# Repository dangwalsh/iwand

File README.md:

# iWand

iWand is a hand-held device that identifies the color of an object it's pointed at. Point it at something, press the button, and it announces the color out loud.

## Repo layout

- [`firmware/`](firmware/README.md) — embedded code for the Seeed XIAO ESP32S3, using a GY-33 color sensor and a DFPlayer Mini + speaker for audio announcement
- [`electrical/`](electrical/README.md) — KiCad project: schematic, routed 75.9 × 22 mm two-layer PCB, project footprint library (`iwand.pretty`), 3D models, and ready-to-order Gerbers (`fab/iwand-gerbers.zip`)
- [`mechanical/`](mechanical/README.md) — enclosure design in Onshape, with a STEP model of the populated PCB (`iwand-pcb.step`) exported from KiCad

Each directory's README has setup/dependency details specific to that part of the project; [`CLAUDE.md`](CLAUDE.md) has the full architecture writeup (wake/sleep flow, pin assignments, library APIs).

## Status

- **Firmware:** a single-file sketch. It runs on hardware with calibration and spoken prompts. The battery-voltage monitor (D10) isn't read yet.
- **Electrical:** the PCB is routed and passes KiCad's design rules and schematic parity checks, with Gerbers ready to order. It hasn't been built or tested yet.
- **Mechanical:** enclosure design in Onshape has just started, from the exported PCB model. The layout along the wand, the component sizes and the required openings are in `mechanical/README.md`.

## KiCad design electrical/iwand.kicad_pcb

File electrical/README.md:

# iWand Electrical

KiCad schematic for the iWand color-identifying wand (Seeed XIAO ESP32S3 + GY-33 color sensor + DFPlayer Mini + AO3400 power gating). See `firmware/CLAUDE.md` for how the pin assignments here map to the firmware.

## Dependencies

- **KiCad 7.0 or newer** (developed with KiCad 10). The schematic (`iwand.kicad_sch`) is in the KiCad 7 s-expression format (`version 20230121`). Older KiCad versions won't open it.

The module symbols (`wand_parts:XIAO_ESP32S3`, `wand_parts:DFPlayer_Mini`) are embedded directly in `iwand.kicad_sch`, so there's no external symbol library to install. ERC warns that the `wand_parts` library isn't configured and that `Device:Q_NMOS_GDS` is missing from KiCad's current `Device` library. Both warnings are harmless, because the embedded copies are used.

## Footprints

Project footprints live in `iwand.pretty`, registered through the project's `fp-lib-table` as `iwand`:

| Footprint | Used by | Source |
|---|---|---|
| `XIAO_ESP32S3_Socket` | U1 | Pad positions from Seeed's `XIAO-ESP32-S3-DIP`, without its castellated SMD pads. USB-C is at +X; B+/B- on the fab layer mark the underside battery pads. |
| `DFPlayer_Mini_Socket` | U3 | DFR0299 datasheet drawing: 20.32 mm square, 2 x 8 pins, rows 18.034 mm apart. |
| `AO3400_SOT23_Adapter` | Q1, Q2 | 1 x 3 pins in the adapter board's S-D-G order (adapter labels 2-3-1). Pads are numbered for `Q_NMOS_GDS`. The adapter outline (~7.6 x 10 mm) is estimated from a photo. |

Everything else is stock KiCad:
- DIN0207 through-hole resistors, lying flat
- a 3 mm disc capacitor
- a C&K OS102011MA1QN1-style right-angle slide switch
- JST-PH side-entry sockets (J1-J4)
- a JST-PH top-entry socket (J5, B2B-PH-K). It takes the same PHR-2 plug as J1-J4, but a side-entry one doesn't fit between Q2 and SW2.

## Board

The board is 75.9 x 22 mm, laid out as a "spine" along the wand. From the rear:
- J4 battery, J2 speaker and J3 button plugs, facing the rear
- the XIAO, with USB-C over the lower long edge; R1-R6 lie flat underneath it
- Q1/Q2 with J5, SW2 and C1
- the DFPlayer
- J1, facing forward to the GY-33

The module sockets are 3M 929870 low-profile strips, 3.8 mm tall, bought as 10-pin strips and cut to length. In them, the XIAO sits about 6.3 mm up (3.8 mm socket + 2.5 mm pin spacer). Its courtyard therefore covers only its socket strips and USB plug, so parts up to about 5 mm tall can go underneath.

For the 3D view:
- **Sockets:** 3M's STEP model is a 10-pin strip, so the view uses KiCad's 1x7/1x8 socket models scaled to 3.8 mm instead.
- **XIAO:** Seeed's STEP file (in `3dmodels/`), drawn 6.3 mm up. The pin spacer under it isn't modelled.
- **DFPlayer:** DFRobot's DFR0299 STEP file (in `3dmodels/`, drawn in inches, Y-up). It includes the module's own pin header, with its spacer resting on the socket top. Its microSD slot opens toward the front of the board, facing J1.

Do a dry fit before soldering. A standard 6 mm male pin may bottom out in a 3.8 mm socket and ride slightly higher than 6.3 mm.

## Mounting and off-board parts

- U1 and U3 plug into female header sockets so they stay removable. Q1/Q2 are AO3400s already soldered to SOT-23 adapter boards, which are mounted flat on their pins.
- The GY-33, speaker, wake button and battery sit off the board on JST-PH connectors:
  - **J1 (GY-33):** a 4-wire pigtail soldered into the sensor's GND/DR/CT/VCC holes, in that order.
  - **J2:** speaker.
  - **J3:** wake button.
  - **J4:** LiPo.
- JST battery polarity isn't standardised. Check each battery against the board's +/- marks before plugging it in. They're on the front, between J4 and the XIAO socket, and on the back next to `BAT`.
  - J4 puts + on pin 1, which is the reverse of most LiPo plugs (black/GND on the left). Such a battery needs the two crimps swapped in its JST housing.
  - Boards fabricated before the back-side marks were added only have the small front marks, which the J4 housing hides.
- The XIAO's battery pads are on its underside, not on its headers. **J5** takes a short JST-PH pigtail soldered to those BAT+/BAT- pads (pin 1 = BAT+) so the XIAO can run from, and charge, the battery on J4.

## Power and charging

- The battery stays in the wand and charges through the XIAO's USB-C (about 100 mA).
- **SW2** is the power switch, in the battery + lead (J4 → SW2 → VBAT). Off disconnects everything, including the charger, so the battery only charges with SW2 on.
- The XIAO's charge LED sits next to its USB-C port, so the enclosure needs a window or light pipe there.
- **R5/R6** (1M each) divide VBAT by 2 into D10, which is an ADC input. **C1** (100 nF) steadies the reading. The divider draws about 2 µA, and nothing when SW2 is off.

## Routing and fabrication

- **Stack-up:** 2 layers, 1.6 mm. Rules: 0.2 mm clearance, 0.5 mm copper to edge. Every connection is routed. DRC and the schematic parity check pass with no errors.
- **Net classes:**
  - **Default:** 0.25 mm tracks, 0.6/0.3 mm vias.
  - **Power:** 0.5 mm tracks, 0.8/0.4 mm vias. Covers `VBAT`, `BAT_IN`, `GND`, `SPK1`/`SPK2`, `AUDIO_GND` and `SENSOR_GND`. Branches to R5/R6/C1 and the gate resistors use 0.25 mm, since they carry almost no current.
- **Module socket pads:** 1.6 mm, so a 0.25 mm track can pass between two 2.54 mm-pitch pins.
- **Ground:** GND pours on both layers, tied together by stitching vias.
- **Fab files:** `fab/iwand-gerbers.zip` (copper, mask, silkscreen, edge cuts, and plated and non-plated drill files). Regenerate it with KiCad's Fabrication Outputs, or with `kicad-cli pcb export gerbers` / `export drill`, after any board change.

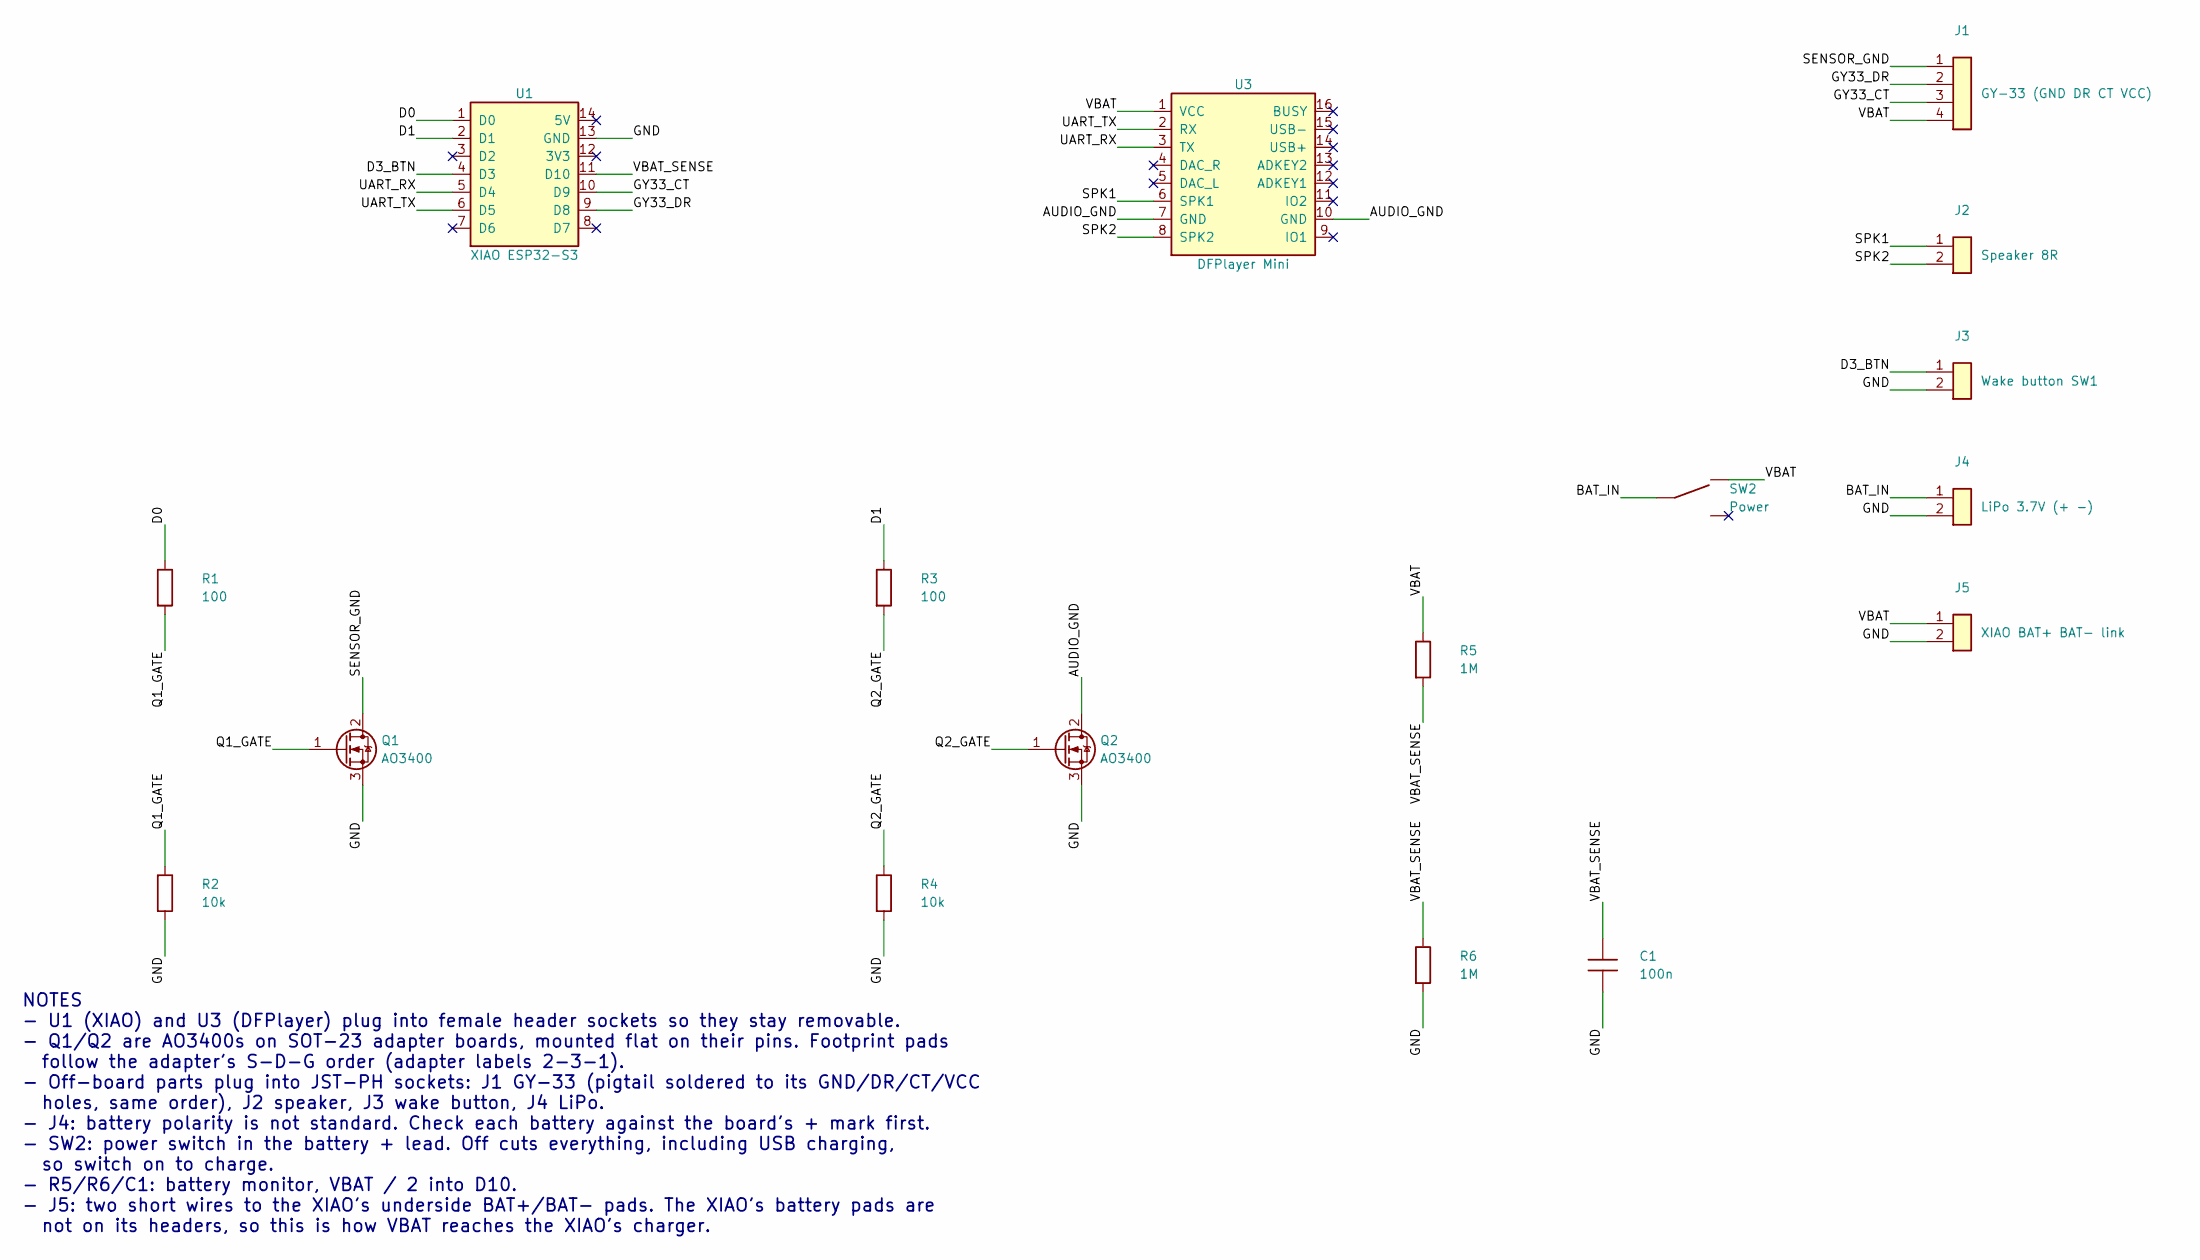
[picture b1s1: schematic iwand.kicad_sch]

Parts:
C1: 100n; C_Disc_D3.0mm_W1.6mm_P2.50mm
J1: GY-33 (GND DR CT VCC); JST_PH_S4B-PH-K_1x04_P2.00mm_Horizontal
J2: Speaker 8R; JST_PH_S2B-PH-K_1x02_P2.00mm_Horizontal
J3: Wake button SW1; JST_PH_S2B-PH-K_1x02_P2.00mm_Horizontal
J4: LiPo 3.7V (+ -); JST_PH_S2B-PH-K_1x02_P2.00mm_Horizontal
J5: XIAO BAT+ BAT- link; JST_PH_B2B-PH-K_1x02_P2.00mm_Vertical
Q1, Q2: AO3400; AO3400_SOT23_Adapter
R1, R3: 100; R_Axial_DIN0207_L6.3mm_D2.5mm_P7.62mm_Horizontal
R2, R4: 10k; R_Axial_DIN0207_L6.3mm_D2.5mm_P7.62mm_Horizontal
R5, R6: 1M; R_Axial_DIN0207_L6.3mm_D2.5mm_P7.62mm_Horizontal
SW2: Power; SW_Slide_SPDT_Angled_CK_OS102011MA1Q
U1: XIAO ESP32-S3; XIAO_ESP32S3_Socket
U3: DFPlayer Mini; DFPlayer_Mini_Socket

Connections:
/AUDIO_GND: Q2.2 (D), U3.7 (GND), U3.10 (GND)
/BAT_IN: J4.1, SW2.2 (B)
/D0: R1.1, U1.1 (D0)
/D1: R3.1, U1.2 (D1)
/D3_BTN: J3.1, U1.4 (D3)
/GND: C1.2, J3.2, J4.2, J5.2, Q1.3 (S), Q2.3 (S), R2.2, R4.2, R6.2, U1.13 (GND)
/GY33_CT: J1.3, U1.10 (D9)
/GY33_DR: J1.2, U1.9 (D8)
/Q1_GATE: Q1.1 (G), R1.2, R2.1
/Q2_GATE: Q2.1 (G), R3.2, R4.1
/SENSOR_GND: J1.1, Q1.2 (D)
/SPK1: J2.1, U3.6 (SPK1)
/SPK2: J2.2, U3.8 (SPK2)
/UART_RX: U1.5 (D4), U3.3 (TX)
/UART_TX: U1.6 (D5), U3.2 (RX)
/VBAT: J1.4, J5.1, R5.1, SW2.1 (A), U3.1 (VCC)
/VBAT_SENSE: C1.1, R5.2, R6.1, U1.11 (D10)

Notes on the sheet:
NOTES - U1 (XIAO) and U3 (DFPlayer) plug into female header sockets so they stay removable. - Q1/Q2 are AO3400s on SOT-23 adapter boards, mounted flat on their pins. Footprint pads follow the adapter's S-D-G order (adapter labels 2-3-1). - Off-board parts plug into JST-PH sockets: J1 GY-33 (pigtail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

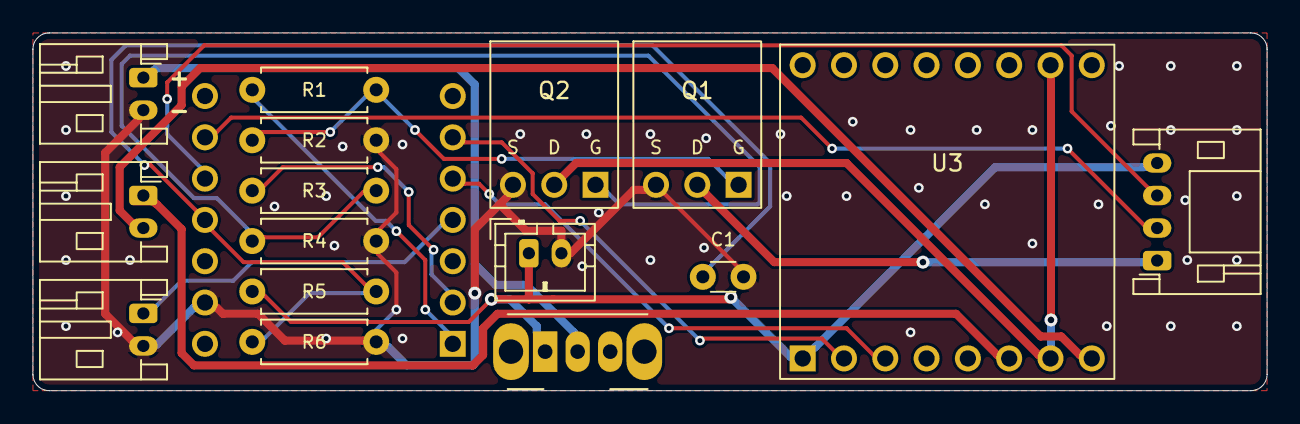
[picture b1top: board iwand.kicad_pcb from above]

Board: 2 copper layers, 75.9 x 22.0 mm, 17 parts (0 on the bottom side), 17 nets.
